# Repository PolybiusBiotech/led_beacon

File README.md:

# 🚨 LED Beacon 🚨

Upgrading cheap LED beacons for professional DMX/Art-Net stage control.

## 🚀 Manufacturing Status
- **Design:** Completed
- **Prototyping:** Completed
- **Production:** Completed

## 📋 Quick Specs
- **Power:** +12V ±30% @ 2A
- **LEDS:** 10x strings of 6 LEDs
- **MCU:** ESP32-C3-WROOM-02
- **Connectivity:** DMX512 via 5 pin XLRs and WiFi

## 📂 Project Structure
- `/hardware`: KiCAD project files (Version 9.0.7).
- `/firmware`: PlatformIO project (Arduino/ESP-IDF framework).
- `/mechanical`: 3D-printable housing (.STEP).
- `/docs`: Specification, schematics and design calculations.
<!-- test: for test scripts -->

## 🛠 Setup & Development

### Hardware
- **Library Dependencies:** All footprints/symbols are [local to the repo / use standard KiCAD libs].
- **CI/CD:** Schematics are automatically exported to `/docs` on every push.

### Firmware
1. Open the `/firmware` folder in **VS Code**.
2. Ensure the **PlatformIO** extension is installed.
3. Connect your hardware via USB C port and click **Upload**.

## 📝 User Guide

1. Apply power via DC connector, 12V ±30% from a 3A capable supply.
2. Attach to DMX chain with 2x XLR 5pin cables
   * If at the end of the bus use a terminator plug
3. Select a DMX address with the DIP switch
   * This light consumes 20 slots so avoid address above 492.
   * Ensure that this light is >20 slots away from the next lights.
   * Light checks DIP switch and updated the DMX address every 2.5seconds.
4. Disable the WiFi AP with the DIP switch unless needed for diagnostics
5. Use your DMX controller to send packets on the DMX chain.
   * Slots 1 to 10 control the brightness per channel
     * `0x00` is off
     * `0xFF` is full brightness
   * Slots 11 to 20 control the strobe effect per channel
     * `0x00` is fully on
     * `0x01` strobes at 0.2Hz
     * `0xFF` strobes at 20Hz
6. Enjoy!

---
*Commissioned for Null Sector for EMF Camp 2026.*

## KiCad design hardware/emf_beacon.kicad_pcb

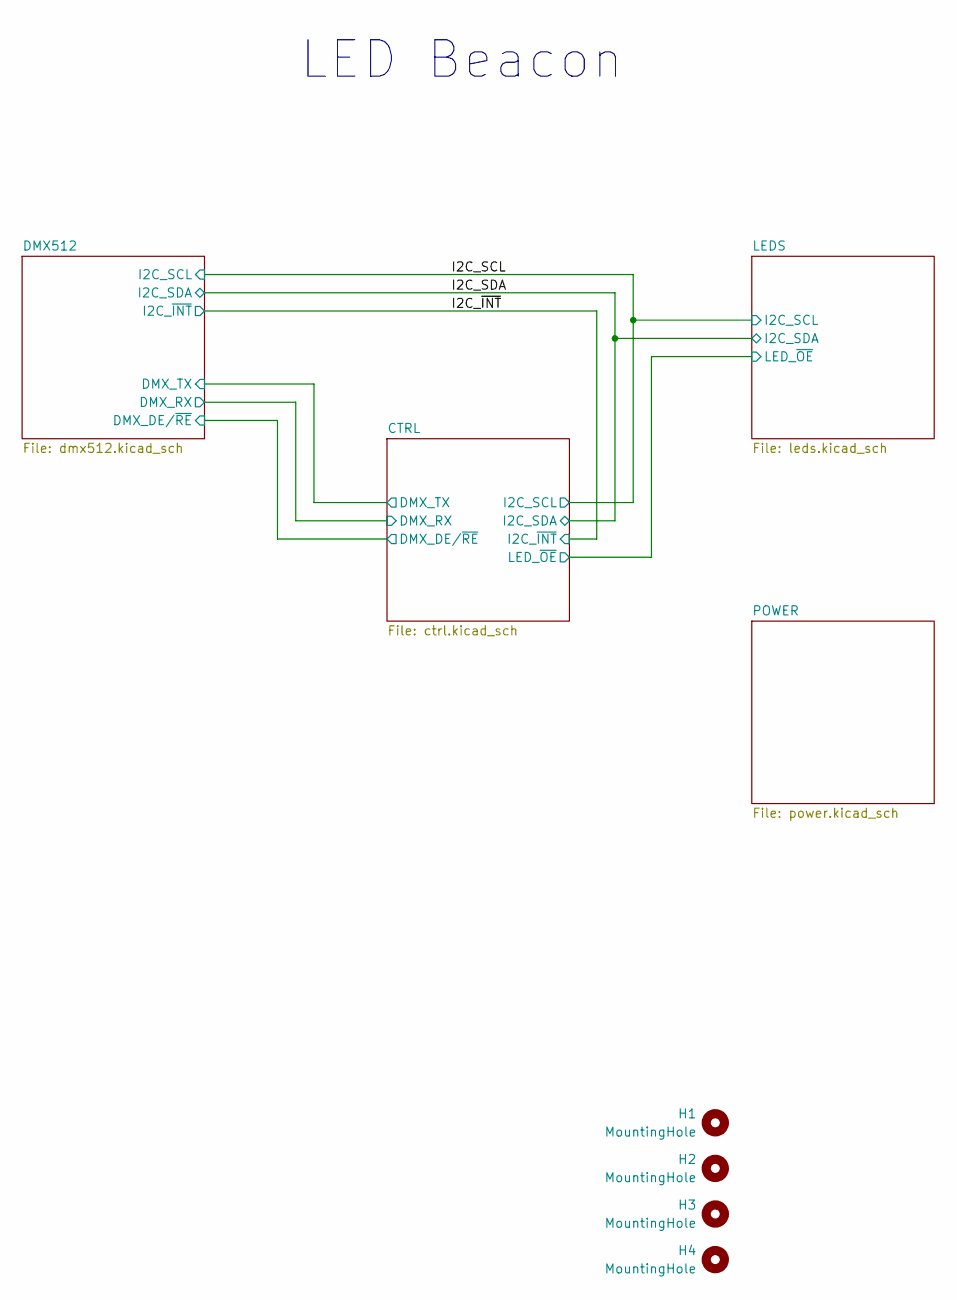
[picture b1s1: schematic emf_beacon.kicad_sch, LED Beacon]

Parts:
H1, H2, H3, H4: MountingHole; MountingHole_4.3mm_M4

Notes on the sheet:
LED Beacon

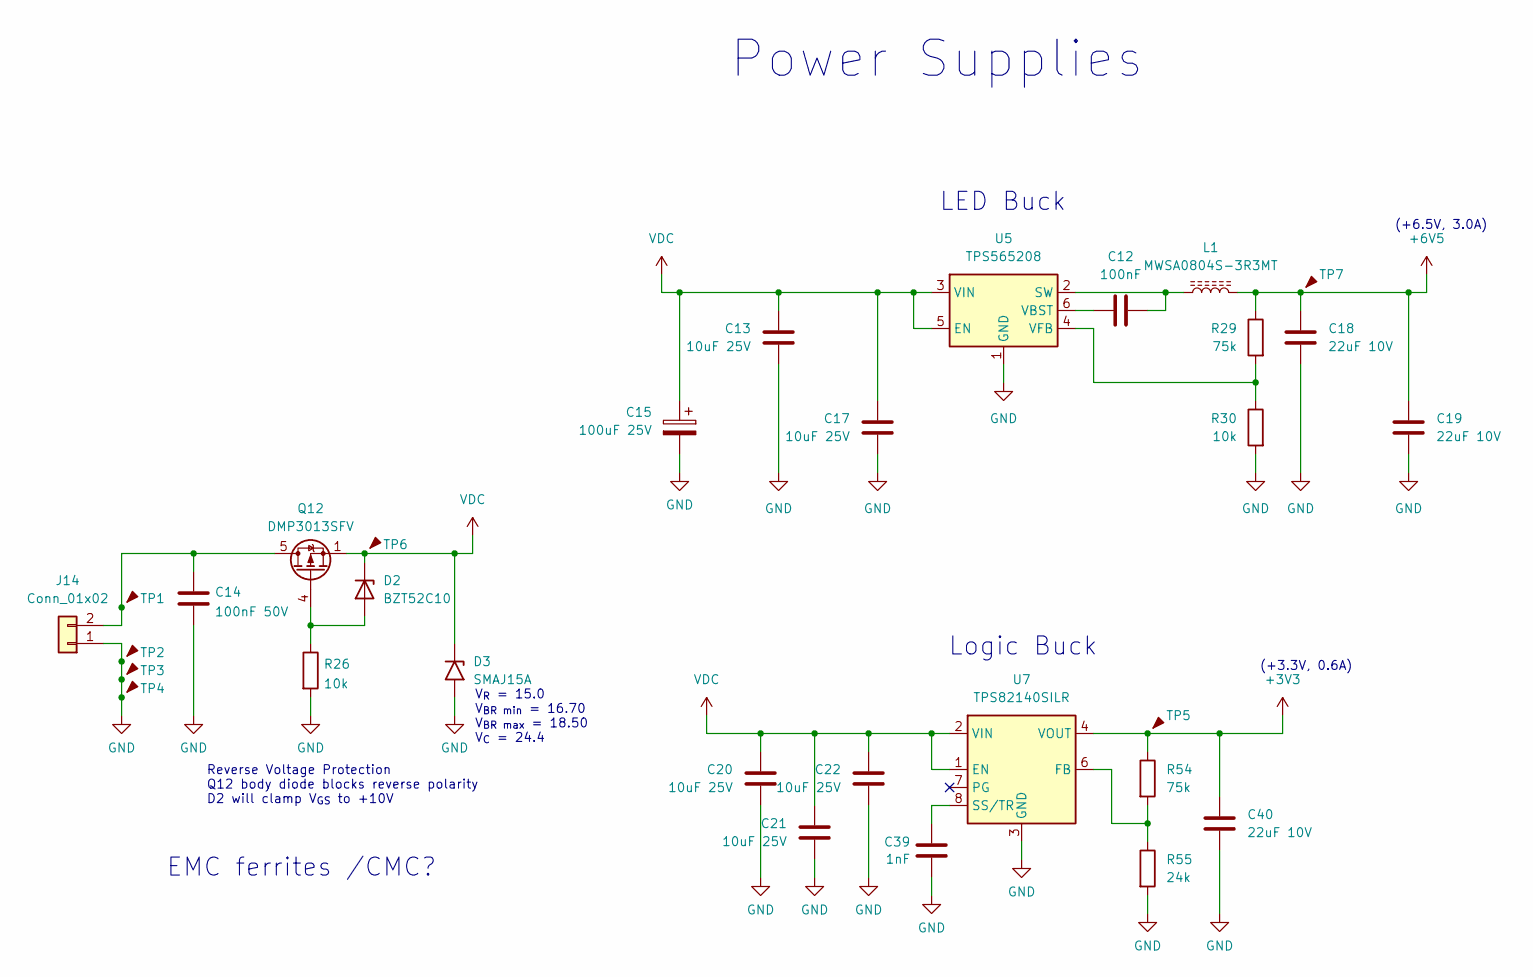
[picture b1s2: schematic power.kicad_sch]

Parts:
C12: 100nF; C_0603_1608Metric; LCSC C14663
C13, C17, C20, C21, C22: 10uF 25V; C_0805_2012Metric; LCSC C15850
C14: 100nF 50V; C_0603_1608Metric; LCSC C14663
C15: 100uF 25V; CP_Elec_6.3x7.7; LCSC C267469
C18, C19: 22uF 10V; C_0805_2012Metric; LCSC C45783
C39: 1nF; C_0603_1608Metric; Voltage 50V; LCSC C1588
C40: 22uF 10V; C_0805_2012Metric; Voltage 10V; LCSC C45783
D2: BZT52C10; D_SOD-123; LCSC C19077408
D3: SMAJ15A; D_SMA; LCSC C19077535
J14: Conn_01x02; MX250-3.5-02P-A-GY01-Cu-A; LCSC C7467028
L1: MWSA0804S-3R3MT; L_Vishay_IHLP-3232; LCSC C17700166
Q12: DMP3013SFV; Diodes_PowerDI3333-8; LCSC C49452326
R26, R30: 10k; R_0603_1608Metric; LCSC C25804
R29, R54: 75k; R_0603_1608Metric; LCSC C23242
R55: 24k; R_0603_1608Metric; LCSC C23352
TP1, TP2, TP3, TP4, TP5, TP6, TP7: TestPoint; TestPoint_Pad_D1.5mm
U5: TPS565208; SOT-23-6; LCSC C2650336
U7: TPS82140SILR; Texas_SIL0008D_MicroSiP-8-1EP_2.8x3mm_P0.65mm_EP1.1x1.9mm; LCSC C544385

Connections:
+3V3: C40.1, R54.1, TP5.1, U7.4 (VOUT), U7.5 (VOUT); also elsewhere on the board
+6V5: C18.1, C19.1, L1.2, R29.1, TP7.1; also elsewhere on the board
GND: C13.2, C14.2, C15.2, C17.2, C18.2, C19.2, C20.2, C21.2, C22.2, C39.2, C40.2, D3.2 (A2), J14.1, R26.2, R30.2, R55.2, TP2.1, TP3.1, TP4.1, U5.1 (GND), U7.3 (GND), U7.9 (GND); also elsewhere on the board
unnamed: D2.2 (A), Q12.4 (G), R26.1
unnamed: C14.1, J14.2, Q12.5 (D), TP1.1
unnamed: C12.2, L1.1, U5.2 (SW)
unnamed: C12.1, U5.6 (VBST)
unnamed: R29.2, R30.1, U5.4 (VFB)
unnamed: R54.2, R55.1, U7.6 (FB)
unnamed: C39.1, U7.8 (SS/TR)
VDC: C13.1, C15.1, C17.1, C20.1, C21.1, C22.1, D2.1 (K), D3.1 (A1), Q12.1 (S), Q12.2 (S), Q12.3 (S), TP6.1, U5.3 (VIN), U5.5 (EN), U7.1 (EN), U7.2 (VIN); also elsewhere on the board

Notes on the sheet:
LED Buck
Power Supplies
V_{R} = 15.0 V_{BR min} = 16.70 V_{BR max} = 18.50 V_{C} = 24.4
Logic Buck
(+6.5V, 3.0A)
EMC ferrites /CMC?
Reverse Voltage Protection Q12 body diode blocks reverse polarity D2 will clamp V_{GS} to +10V
(+3.3V, 0.6A)

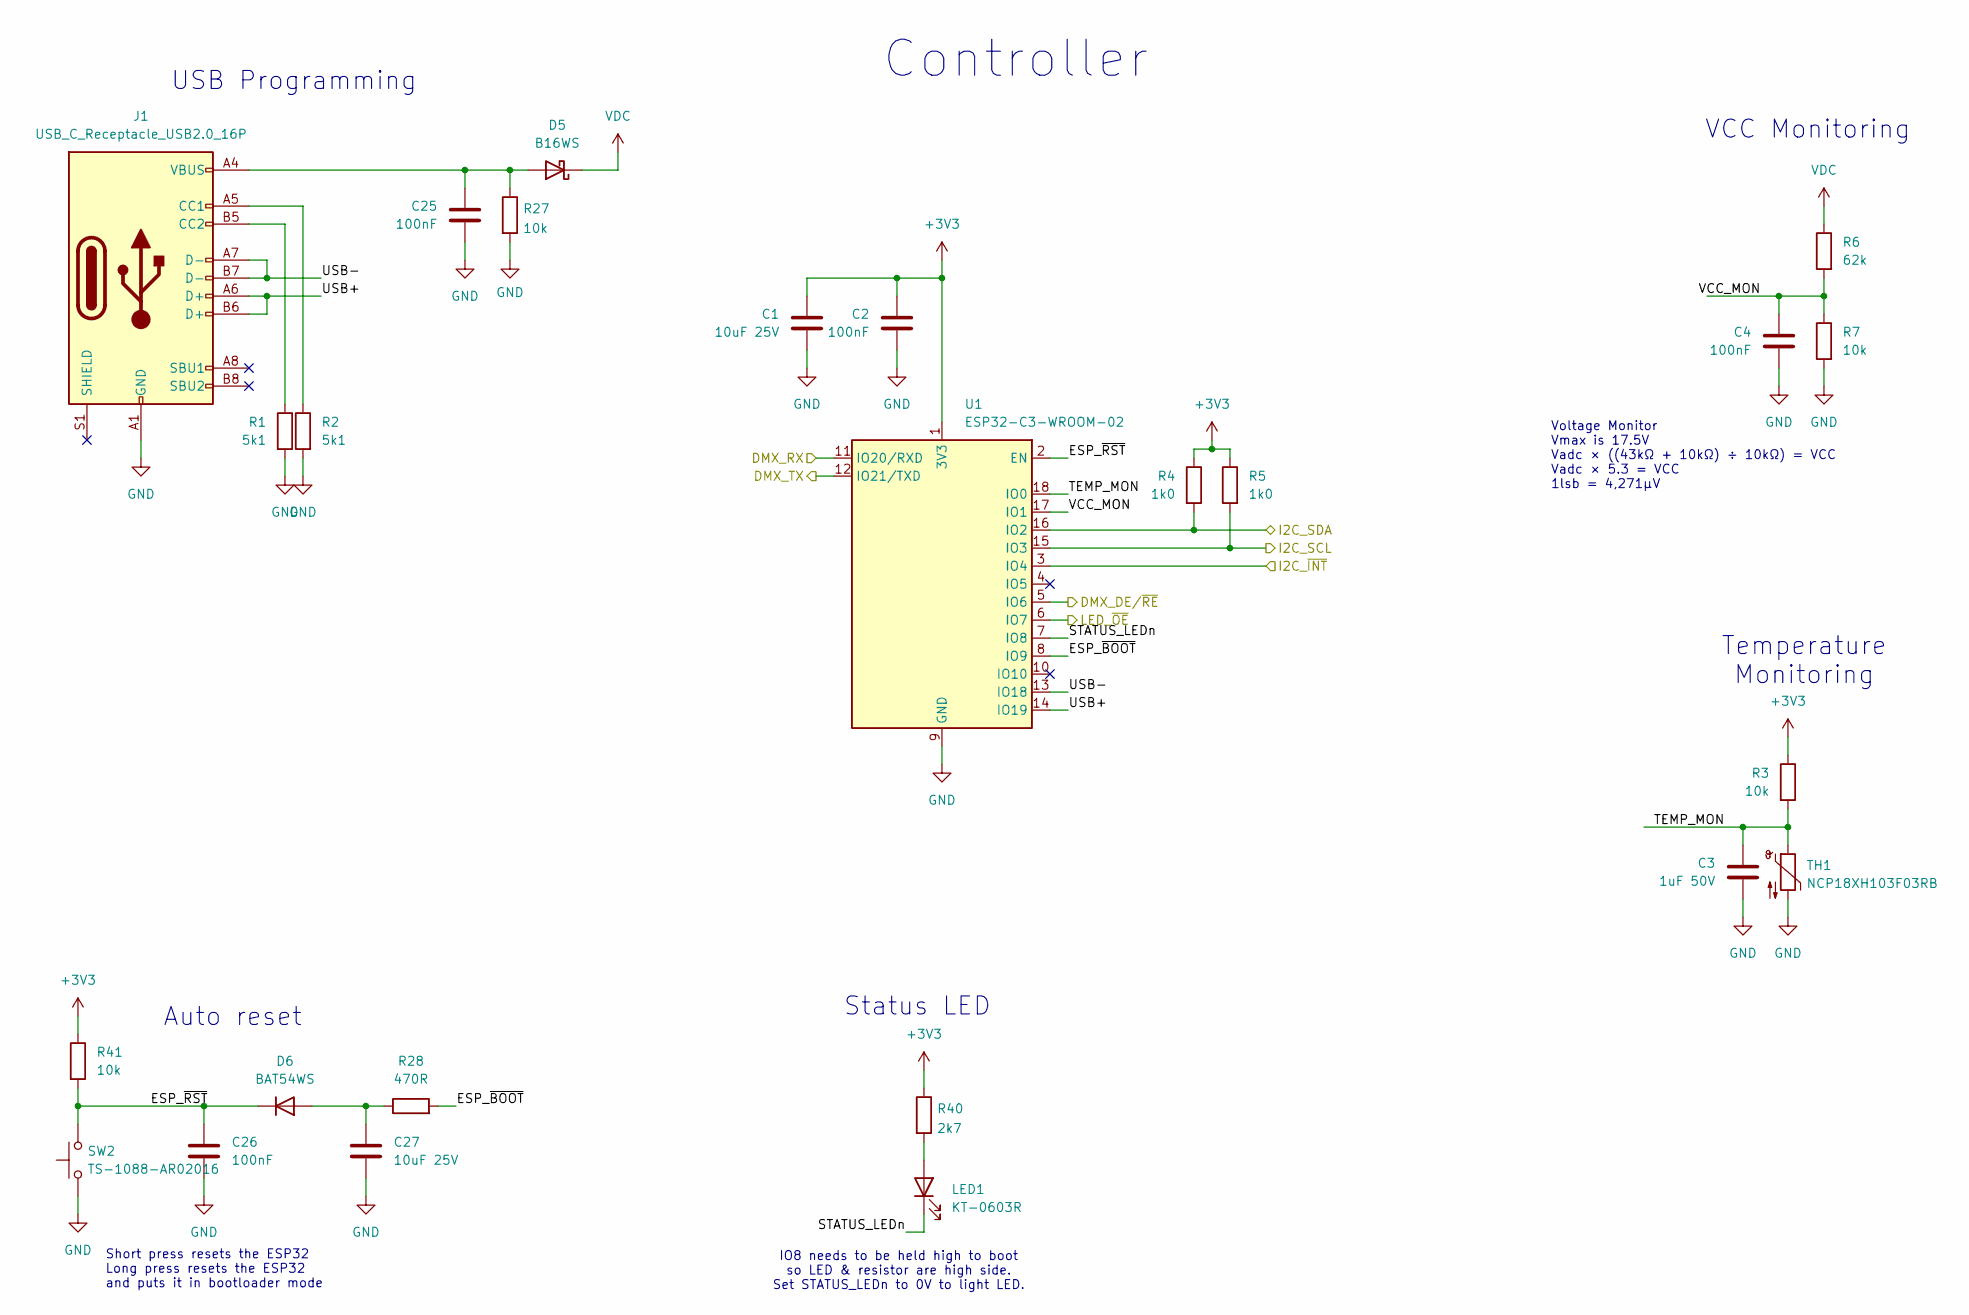
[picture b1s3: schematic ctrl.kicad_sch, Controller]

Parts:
C1, C27: 10uF 25V; C_0805_2012Metric; LCSC C15850
C2, C4, C25, C26: 100nF; C_0603_1608Metric; LCSC C14663
C3: 1uF 50V; C_0603_1608Metric; LCSC C15849
D5: B16WS; D_SOD-323; LCSC C7420327
D6: BAT54WS; D_SOD-323; LCSC C7502694
J1: USB_C_Receptacle_USB2.0_16P; USB_C_Receptacle_HCTL_HC-TYPE-C-16P-01A; LCSC C393939
LED1: KT-0603R; LED_0603_1608Metric; LCSC C2286
R1, R2: 5k1; R_0603_1608Metric; LCSC C23186
R3, R7, R27, R41: 10k; R_0603_1608Metric; LCSC C25804
R4, R5: 1k0; R_0603_1608Metric; LCSC C21190
R6: 62k; R_0603_1608Metric; LCSC C23221
R28: 470R; R_0603_1608Metric; LCSC C23179
R40: 2k7; R_0603_1608Metric; LCSC C13167
SW2: TS-1088-AR02016; SW_Push_SPST_NO_Alps_SKRK; LCSC C720477
TH1: NCP18XH103F03RB; R_0603_1608Metric; MPN NCP18XH103F03RB; LCSC C13564
U1: ESP32-C3-WROOM-02; LCSC C2934560

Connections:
+3V3: C1.1, C2.1, R3.1, R4.1, R5.1, R40.1, R41.1, U1.1 (3V3); also elsewhere on the board
/CTRL/DMX_DE/~RE: U1.5 (IO6); also elsewhere on the board
/CTRL/DMX_RX: U1.11 (IO20/RXD); also elsewhere on the board
/CTRL/DMX_TX: U1.12 (IO21/TXD); also elsewhere on the board
/CTRL/ESP_~BOOT: R28.2, U1.8 (IO9)
/CTRL/ESP_~RST: C26.1, D6.1 (K), R41.2, SW2.2, U1.2 (EN)
/CTRL/LED_~OE: U1.6 (IO7); also elsewhere on the board
/CTRL/STATUS_LEDn: LED1.1 (K), U1.7 (IO8)
/CTRL/TEMP_MON: C3.1, R3.2, TH1.1, U1.18 (IO0)
/CTRL/USB+: J1.A6 (D+), J1.B6 (D+), U1.14 (IO19)
/CTRL/USB-: J1.A7 (D-), J1.B7 (D-), U1.13 (IO18)
/CTRL/VCC_MON: C4.1, R6.2, R7.1, U1.17 (IO1)
/I2C_SCL: R5.2, U1.15 (IO3); also elsewhere on the board
/I2C_SDA: R4.2, U1.16 (IO2); also elsewhere on the board
/I2C_~INT: U1.3 (IO4); also elsewhere on the board
GND: C1.2, C2.2, C3.2, C4.2, C25.2, C26.2, C27.2, J1.A1 (GND), J1.A12 (GND), J1.B1 (GND), J1.B12 (GND), R1.2, R2.2, R7.2, R27.2, SW2.1, TH1.2, U1.9 (GND), U1.19 (GND); also elsewhere on the board
unnamed: C25.1, D5.2 (A), J1.A4 (VBUS), J1.A9 (VBUS), J1.B4 (VBUS), J1.B9 (VBUS), R27.1
unnamed: C27.1, D6.2 (A), R28.1
unnamed: J1.A5 (CC1), R2.1
unnamed: J1.B5 (CC2), R1.1
unnamed: LED1.2 (A), R40.2
VDC: D5.1 (K), R6.1; also elsewhere on the board

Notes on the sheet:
Auto reset
VCC Monitoring
Status LED
Short press resets the ESP32 Long press resets the ESP32 and puts it in bootloader mode
Temperature Monitoring
USB Programming
Controller
IO8 needs to be held high to boot so LED & resistor are high side. Set STATUS_LEDn to 0V to light LED.
Voltage Monitor Vmax is 17.5V Vadc × ((43kΩ + 10kΩ) ÷ 10kΩ) = VCC Vadc × 5.3 = VCC 1lsb = 4,271μV

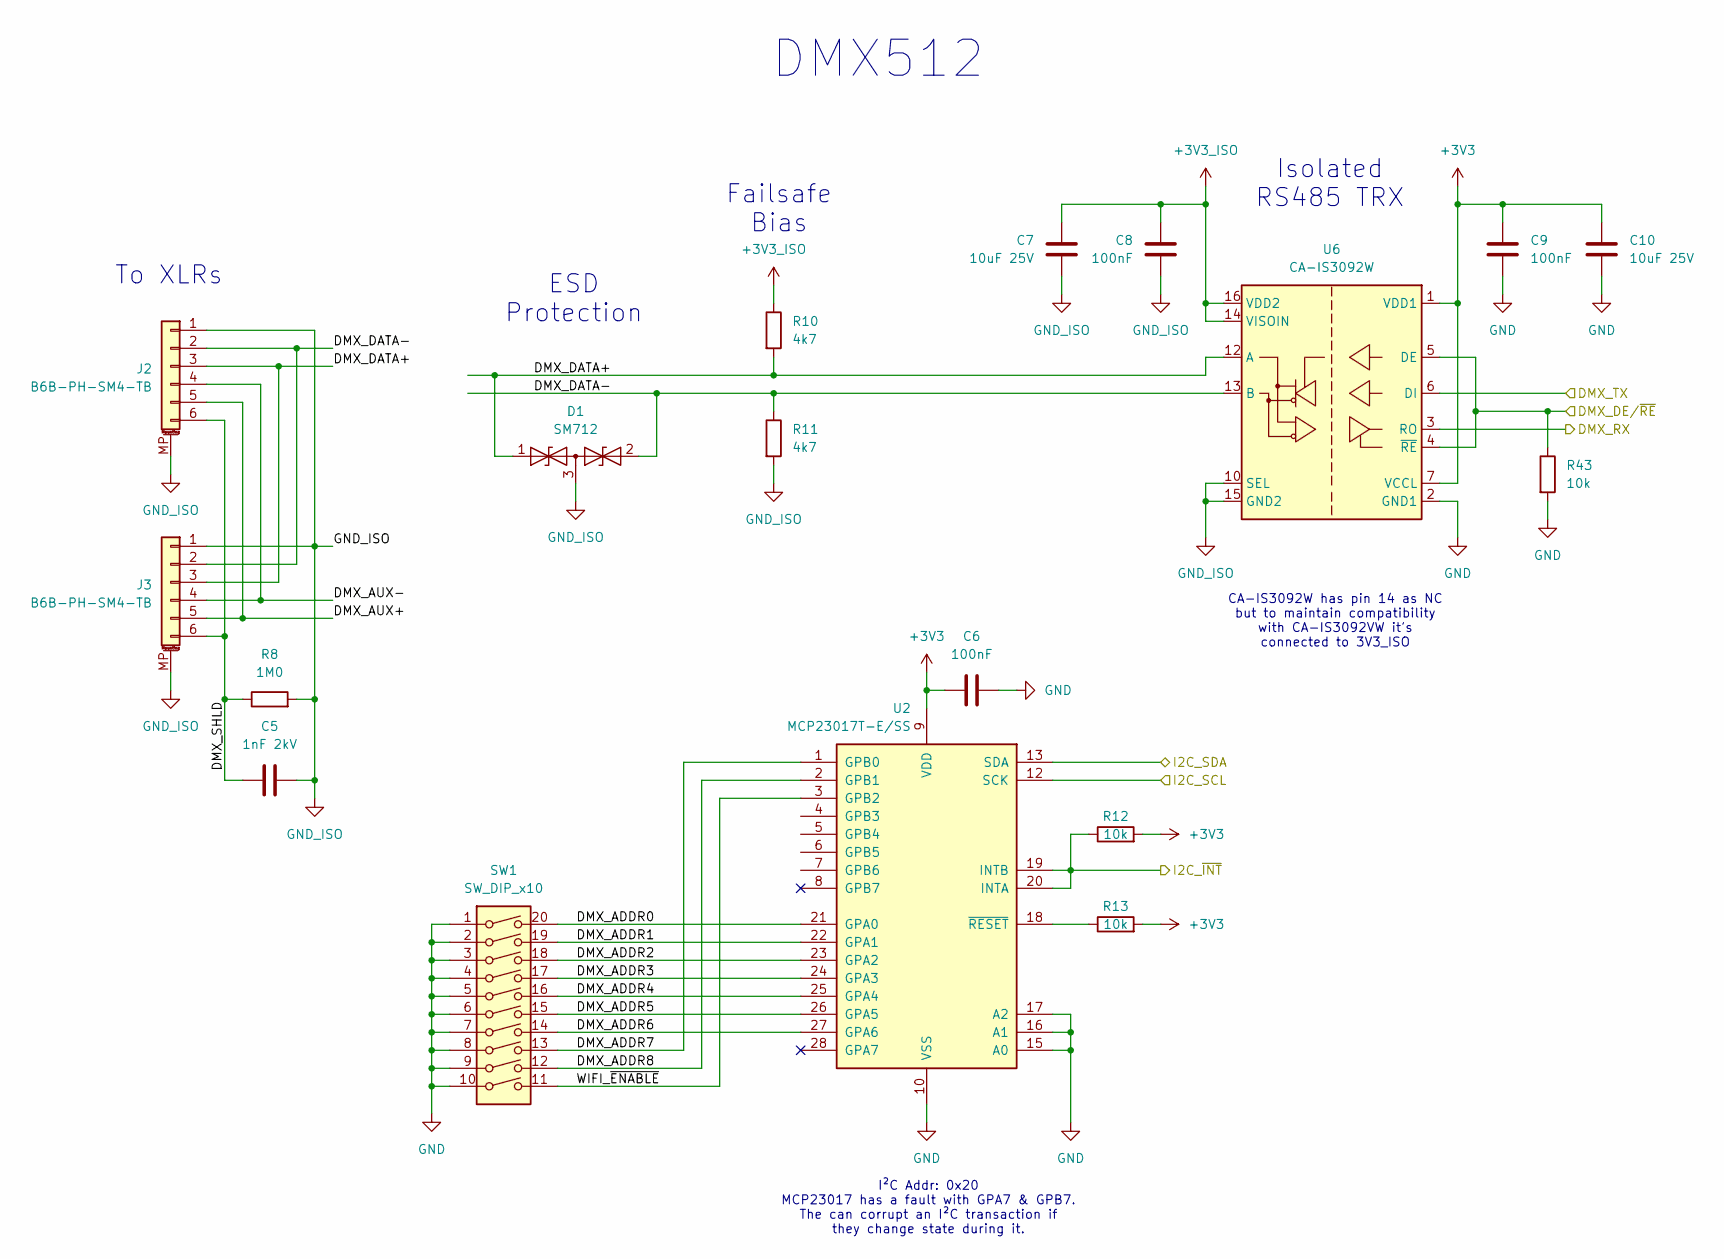
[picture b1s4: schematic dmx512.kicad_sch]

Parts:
C5: 1nF 2kV; C_1206_3216Metric; LCSC C9196
C6, C8, C9: 100nF; C_0603_1608Metric; LCSC C14663
C7, C10: 10uF 25V; C_0805_2012Metric; LCSC C15850
D1: SM712; SOT-23; LCSC C7420375
J2, J3: B6B-PH-SM4-TB; JST_PH_B6B-PH-SM4-TB_1x06-1MP_P2.00mm_Vertical; LCSC C471518
R8: 1M0; R_1206_3216Metric; LCSC C17927
R10, R11: 4k7; R_0603_1608Metric; LCSC C23162
R12, R13, R43: 10k; R_0603_1608Metric; LCSC C25804
SW1: SW_DIP_x10; SW_DIP_SPSTx10_Slide_9.78x27.58mm_W7.62mm_P2.54mm; LCSC C509577
U2: MCP23017T-E/SS; SSOP-28_5.3x10.2mm_P0.65mm; LCSC C558584
U6: CA-IS3092W; SOIC-16W_7.5x10.3mm_P1.27mm; LCSC C2890051

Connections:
+3V3: C6.2, C9.1, C10.1, R12.2, R13.2, U2.9 (VDD), U6.1 (VDD1), U6.7 (VCCL); also elsewhere on the board
+3V3_ISO: C7.1, C8.1, R10.1, U6.14 (VISOIN), U6.16 (VDD2)
/CTRL/DMX_DE/~RE: R43.1, U6.4 (~RE), U6.5 (DE); also elsewhere on the board
/CTRL/DMX_RX: U6.3 (RO); also elsewhere on the board
/CTRL/DMX_TX: U6.6 (DI); also elsewhere on the board
/DMX512/DMX_ADDR0: SW1.20, U2.21 (GPA0)
/DMX512/DMX_ADDR1: SW1.19, U2.22 (GPA1)
/DMX512/DMX_ADDR2: SW1.18, U2.23 (GPA2)
/DMX512/DMX_ADDR3: SW1.17, U2.24 (GPA3)
/DMX512/DMX_ADDR4: SW1.16, U2.25 (GPA4)
/DMX512/DMX_ADDR5: SW1.15, U2.26 (GPA5)
/DMX512/DMX_ADDR6: SW1.14, U2.27 (GPA6)
/DMX512/DMX_ADDR7: SW1.13, U2.1 (GPB0)
/DMX512/DMX_ADDR8: SW1.12, U2.2 (GPB1)
/DMX512/DMX_AUX+: J2.5, J3.5
/DMX512/DMX_AUX-: J2.4, J3.4
/DMX512/DMX_DATA+: D1.1 (A1), J2.3, J3.3, R10.2, U6.12 (A)
/DMX512/DMX_DATA-: D1.2 (A2), J2.2, J3.2, R11.1, U6.13 (B)
/DMX512/DMX_SHLD: C5.1, J2.6, J3.6, R8.1
/DMX512/WIFI_~ENABLE: SW1.11, U2.3 (GPB2)
/I2C_SCL: U2.12 (SCK); also elsewhere on the board
/I2C_SDA: U2.13 (SDA); also elsewhere on the board
/I2C_~INT: R12.1, U2.19 (INTB), U2.20 (INTA); also elsewhere on the board
GND: C6.1, C9.2, C10.2, R43.2, SW1.1, SW1.2, SW1.3, SW1.4, SW1.5, SW1.6, SW1.7, SW1.8, SW1.9, SW1.10, U2.10 (VSS), U2.15 (A0), U2.16 (A1), U2.17 (A2), U6.2 (GND1), U6.8 (GND1); also elsewhere on the board
GND_ISO: C5.2, C7.2, C8.2, D1.3 (common), J2.1, J2.MP (MountPin), J3.1, J3.MP (MountPin), R8.2, R11.2, U6.9 (GND2), U6.10 (SEL), U6.15 (GND2)
unnamed: R13.1, U2.18 (~RESET)

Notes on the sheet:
I²C Addr: 0x20 MCP23017 has a fault with GPA7 & GPB7. The can corrupt an I²C transaction if they change state during it.
Failsafe Bias
DMX512
CA-IS3092W has pin 14 as NC but to maintain compatibility with CA-IS3092VW it's connected to 3V3_ISO
To XLRs
ESD Protection
Isolated RS485 TRX

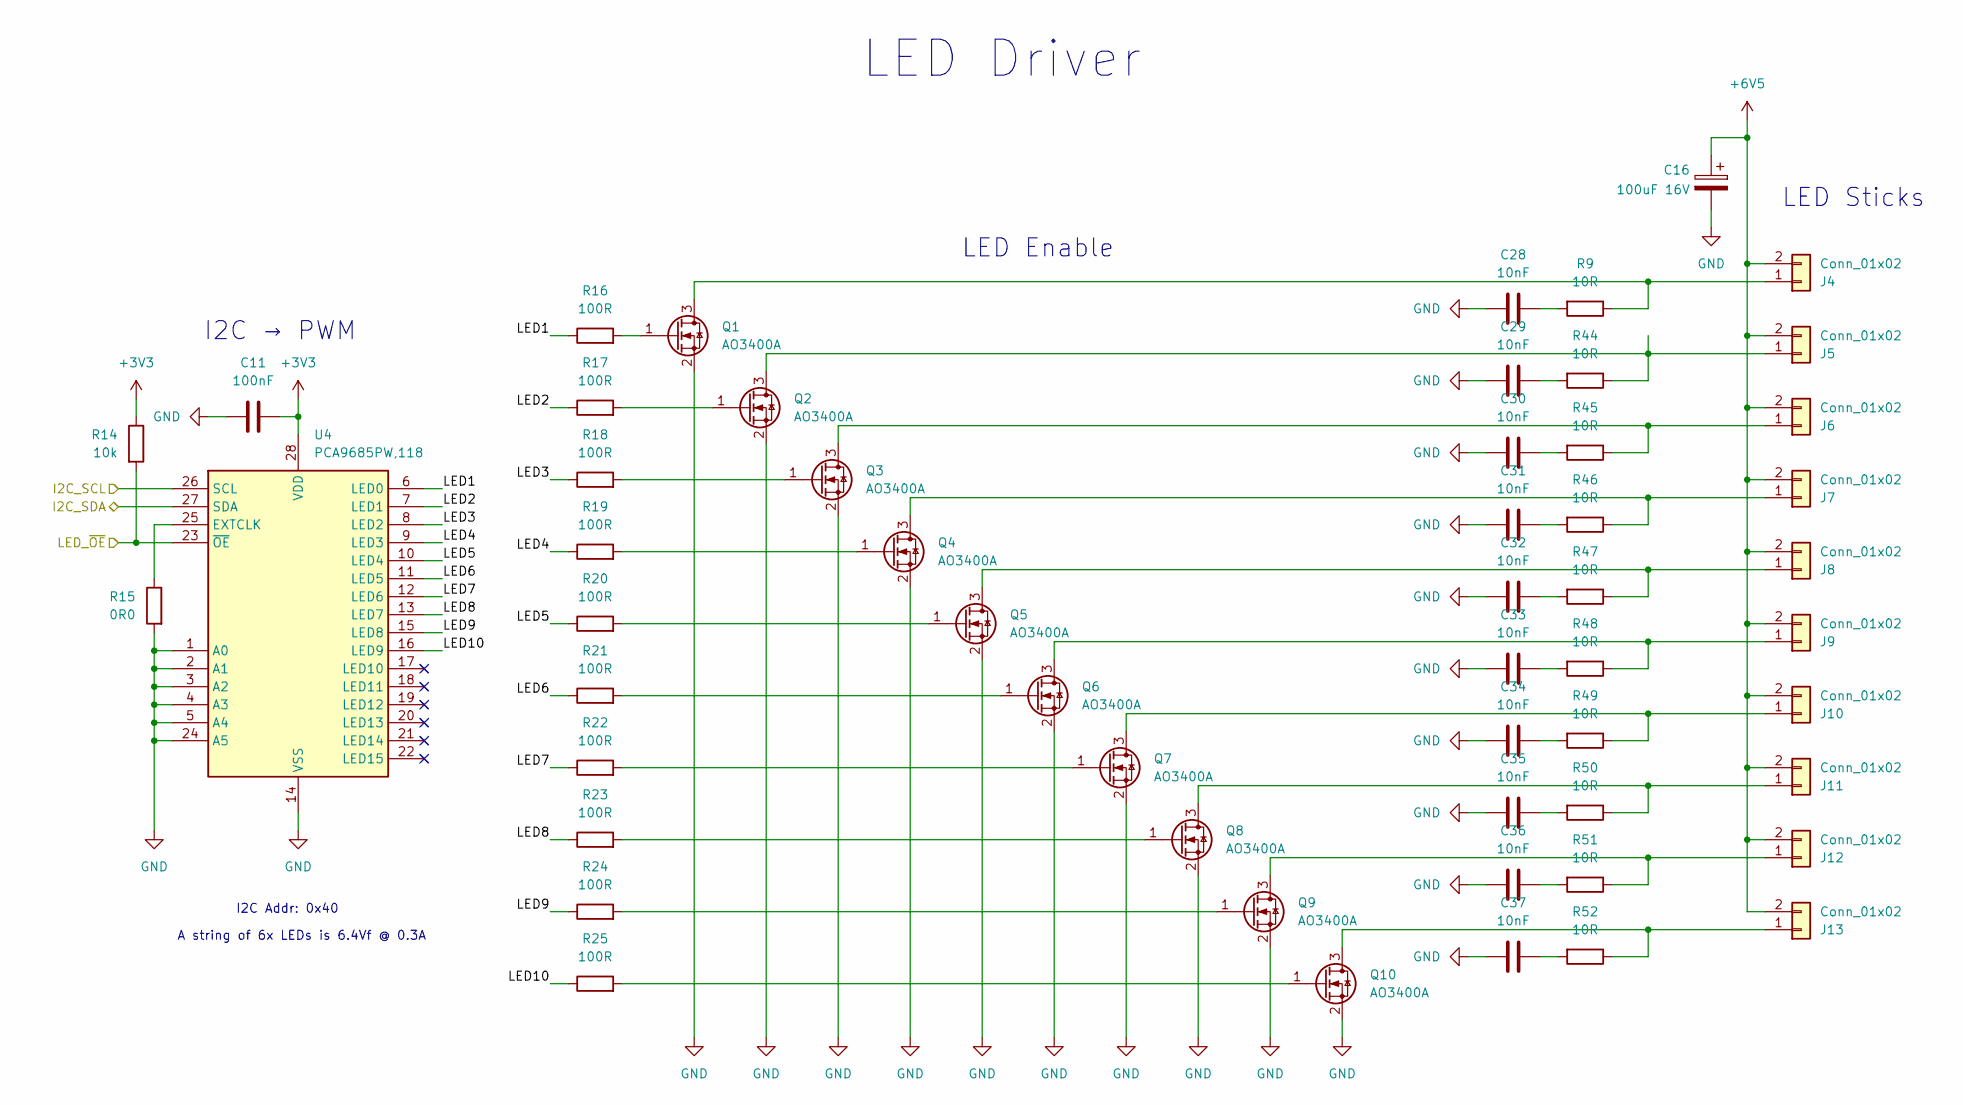
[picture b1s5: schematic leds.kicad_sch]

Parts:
C11: 100nF; C_0603_1608Metric; LCSC C14663
C16: 100uF 16V; CP_Elec_6.3x5.7; LCSC C3646798
C28, C29, C30, C31, C32, C33, C34, C35, C36, C37: 10nF; C_0603_1608Metric; LCSC C57112
J4, J5, J6, J7, J8, J9, J10, J11, J12, J13: Conn_01x02; LED_Stick
Q1, Q2, Q3, Q4, Q5, Q6, Q7, Q8, Q9, Q10: AO3400A; SOT-23; LCSC C20917
R9, R44, R45, R46, R47, R48, R49, R50, R51, R52: 10R; R_0603_1608Metric; LCSC C22859
R14: 10k; R_0603_1608Metric; LCSC C25804
R15: 0R0; R_0603_1608Metric; LCSC C21189
R16, R17, R18, R19, R20, R21, R22, R23, R24, R25: 100R; R_0603_1608Metric; LCSC C22775
U4: PCA9685PW,118; TSSOP-28_4.4x9.7mm_P0.65mm; LCSC C2678753

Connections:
+3V3: C11.2, R14.1, U4.28 (VDD); also elsewhere on the board
+6V5: C16.1, J4.2, J5.2, J6.2, J7.2, J8.2, J9.2, J10.2, J11.2, J12.2, J13.2; also elsewhere on the board
/CTRL/LED_~OE: R14.2, U4.23 (~OE); also elsewhere on the board
/I2C_SCL: U4.26 (SCL); also elsewhere on the board
/I2C_SDA: U4.27 (SDA); also elsewhere on the board
/LEDS/LED1: R16.1, U4.6 (LED0)
/LEDS/LED2: R17.1, U4.7 (LED1)
/LEDS/LED3: R18.1, U4.8 (LED2)
/LEDS/LED4: R19.1, U4.9 (LED3)
/LEDS/LED5: R20.1, U4.10 (LED4)
/LEDS/LED6: R21.1, U4.11 (LED5)
/LEDS/LED7: R22.1, U4.12 (LED6)
/LEDS/LED8: R23.1, U4.13 (LED7)
/LEDS/LED9: R24.1, U4.15 (LED8)
/LEDS/LED10: R25.1, U4.16 (LED9)
GND: C11.1, C16.2, C28.1, C29.1, C30.1, C31.1, C32.1, C33.1, C34.1, C35.1, C36.1, C37.1, Q1.2 (S), Q2.2 (S), Q3.2 (S), Q4.2 (S), Q5.2 (S), Q6.2 (S), Q7.2 (S), Q8.2 (S), Q9.2 (S), Q10.2 (S), R15.2, U4.1 (A0), U4.2 (A1), U4.3 (A2), U4.4 (A3), U4.5 (A4), U4.14 (VSS), U4.24 (A5); also elsewhere on the board
unnamed: C28.2, R9.2
unnamed: C29.2, R44.2
unnamed: C30.2, R45.2
unnamed: C31.2, R46.2
unnamed: C32.2, R47.2
unnamed: C33.2, R48.2
unnamed: C34.2, R49.2
unnamed: C35.2, R50.2
unnamed: C36.2, R51.2
unnamed: C37.2, R52.2
unnamed: J4.1, Q1.3 (D), R9.1
unnamed: J5.1, Q2.3 (D), R44.1
unnamed: J6.1, Q3.3 (D), R45.1
unnamed: J7.1, Q4.3 (D), R46.1
unnamed: J8.1, Q5.3 (D), R47.1
unnamed: J9.1, Q6.3 (D), R48.1
unnamed: J10.1, Q7.3 (D), R49.1
unnamed: J11.1, Q8.3 (D), R50.1
unnamed: J12.1, Q9.3 (D), R51.1
unnamed: J13.1, Q10.3 (D), R52.1
unnamed: Q1.1 (G), R16.2
unnamed: Q2.1 (G), R17.2
unnamed: Q3.1 (G), R18.2
unnamed: Q4.1 (G), R19.2
unnamed: Q5.1 (G), R20.2
unnamed: Q6.1 (G), R21.2
unnamed: Q7.1 (G), R22.2
unnamed: Q8.1 (G), R23.2
unnamed: Q9.1 (G), R24.2
unnamed: Q10.1 (G), R25.2
unnamed: R15.1, U4.25 (EXTCLK)

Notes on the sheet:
I2C → PWM
A string of 6x LEDs is 6.4Vf @ 0.3A
I2C Addr: 0x40
LED Enable
LED Driver
LED Sticks

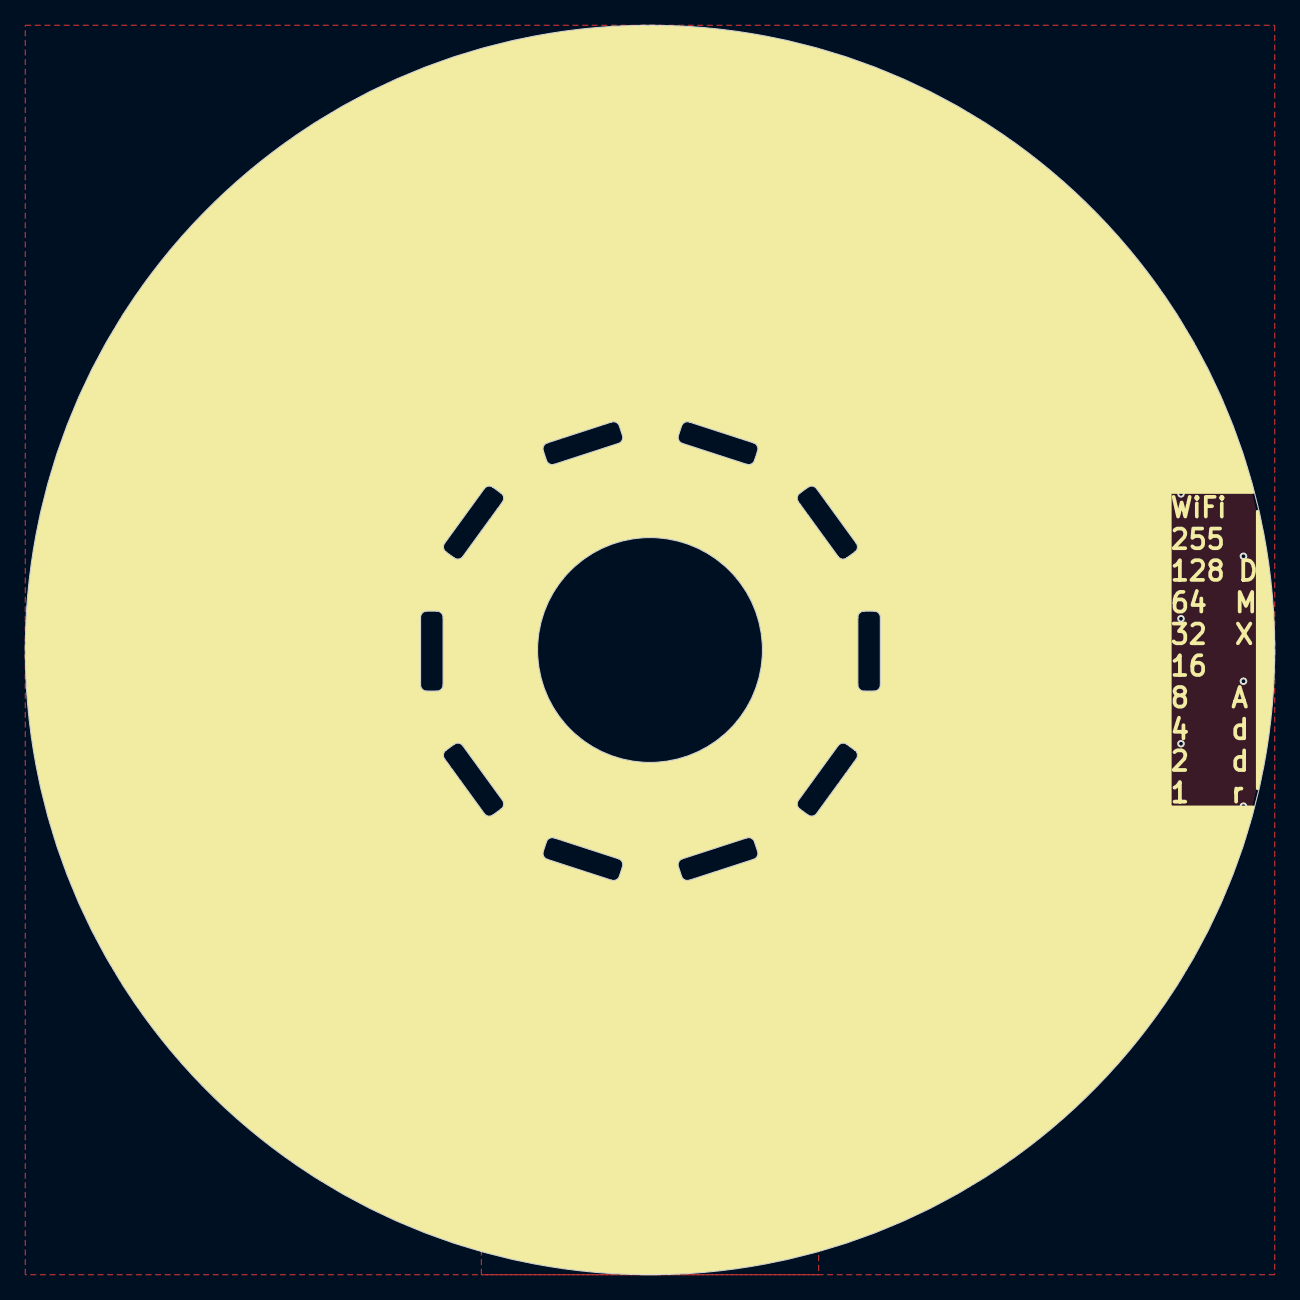
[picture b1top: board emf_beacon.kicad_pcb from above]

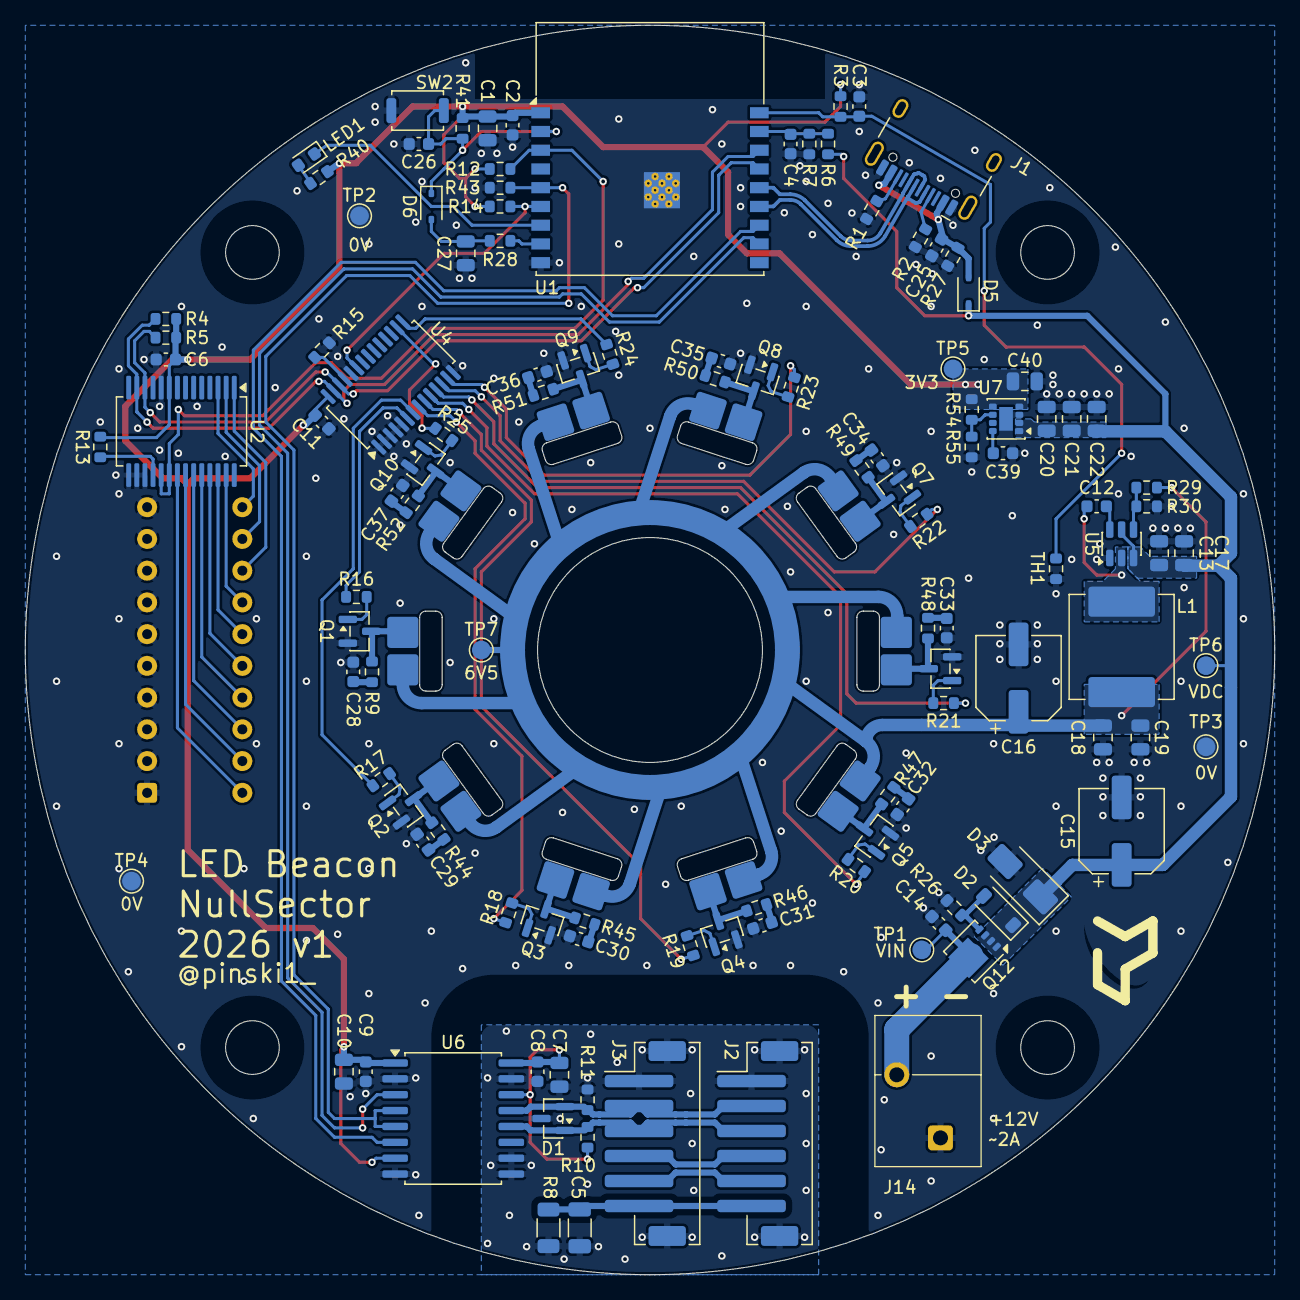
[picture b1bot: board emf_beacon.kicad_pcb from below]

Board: 2 copper layers, 100.0 x 100.0 mm, 133 parts (128 on the bottom side), 89 nets.

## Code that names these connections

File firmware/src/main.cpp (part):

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const char* wifi_pass = "password123";

/** Pin Map **/
#define PIN_TEMP_MON  (0)
#define PIN_VCC_MON   (1)
#define PIN_SDA       (2)
#define PIN_SCL       (3)
#define PIN_I2C_INT   (4)
#define PIN_WIFI_EN   (5)
#define PIN_DMX_EN    (6)
#define PIN_LED_OE    (7)
#define PIN_STATE_LED (8)
#define PIN_DMX_RX   (20)
#define PIN_DMX_TX   (21)

/** Hardware instantiations  **/
Adafruit_PWMServoDriver leds = Adafruit_PWMServoDriver(0x40);
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  Serial.write(init_string);

  // init GPIO
  pinMode(PIN_I2C_INT, INPUT);
  pinMode(PIN_LED_OE, OUTPUT);
  pinMode(PIN_DMX_EN, OUTPUT);
  pinMode(PIN_WIFI_EN, INPUT_PULLUP);
  pinMode(PIN_STATE_LED, OUTPUT);
  digitalWrite(PIN_LED_OE, HIGH);  // disable LEDs
  digitalWrite(PIN_DMX_EN, LOW);
  digitalWrite(PIN_STATE_LED, LOW);
  analogSetAttenuation(ADC_11db);
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  leds.setOutputMode(true);  // LEDs driven by external NMOS
  for (int i = 0; i < led_count; i++) leds.setPWM(i, 0x000, 0x1000);  // sets LED[i]_OFF_H bit
  delay(1);  // takes a PWM cycle to update
  digitalWrite(PIN_LED_OE, LOW);  // enable LEDs!
  Serial.println("PCA9685 initialised...");

  // init DMX
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  };
  int personality_count = 1;
  dmx_driver_install(dmx_num, &config, personalities, personality_count);
  dmx_set_pin(dmx_num, PIN_DMX_TX, PIN_DMX_RX, PIN_DMX_EN);
  Serial.println("DMX initialised...");

  // init Watchdog
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
    // dealing with excessive temp
    if (current_temp >= warning_temp) {
      digitalWrite(PIN_LED_OE, HIGH);  // disable LEDs while too hot!
    } else if (current_temp <= (warning_temp - 5000)) {
      digitalWrite(PIN_LED_OE, LOW);  // enable LEDs now it's cooler
    }

    // not sure what actions to take on over voltage

    // dealing with under voltage
    if (current_volts <= warning_volts) {
      digitalWrite(PIN_LED_OE, HIGH);  // disable LEDs if input voltage is too low!
    } else if (current_volts <= (warning_volts + 3000)) {
      digitalWrite(PIN_LED_OE, LOW);  // enable LEDs now input voltage is higher
    }

    current_uptime = esp_timer_get_time() / 1000000;
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    dmx_adr_switches = (mcp_pin_values & 0x7F) | ((mcp_pin_values & 0x0300) >> 1);
    dmx_address = dmx_adr_switches;  // save DMX address

    wifi_enable = (mcp_pin_values >> 10) & 0x01;

    // enable/disable WiFi AP
    if (wifi_enable && !wifi_ap_active) {
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  int32_t raw_temp = 0x00;

  for (int i = 0; i < 8; i++) {
    raw_temp += analogRead(PIN_TEMP_MON);
    delay(1);
  }
  raw_temp /= 8;
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
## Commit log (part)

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2026-04-20 Adding init files
2026-04-20 inital board files
2026-04-21 adding workflow
2026-04-21 removing 'home' from filenames
2026-04-21 adding ESP32 and PSU options
2026-04-21 docs: auto-generate schematic PDF
2026-04-21 removed Art-Net
2026-04-22 clean up
2026-04-22 updating readme
2026-04-23 adding 3D model of 3D printed beacon base
2026-04-23 inital check in of firmware
2026-04-24 testing PCA9685 and MCP23017 work
2026-04-24 removing I2C scanner
2026-04-25 improving voltage and temperature calcs
2026-04-26 updating thermistor and GPIO expander
2026-04-27 adding LED bightness functionality
2026-04-27 Update main.cpp
    Adding last DMX time to status page
2026-04-27 Update main.cpp
    Told the the server to use the pretty status page.
2026-04-27 adding memory to status page
2026-04-27 adding snubbers, starting placement
2026-04-30 updating PSUs
2026-04-30 adding testing features
2026-04-30 removing art-net.kicad_sch
2026-04-30 some jlc cleanup
2026-04-30 updating documents
2026-05-07 tweaking lcsc part numbers
2026-05-12 Update export_artifacts.yml
    Fixing step export
2026-05-12 docs: auto-generate schematic PDF, 3D model, and rear render
2026-05-12 Adding wiring drawings for XLR pigtails
2026-05-13 general schematic and PCB clean
2026-05-19 Update main.cpp
    Combining memory & system cards
2026-05-21 sorting button and LED
2026-05-24 starting layout
2026-05-25 adding DRU for DMX isolation
2026-05-25 moving all parts into project libraries
2026-05-25 more layout and fixing OOS items
2026-06-02 LEDs connected
2026-06-03 updating DMX TRX and improving silkscreen
2026-06-03 routing VDC
2026-06-03 fixing terminal block pads
2026-06-04 finished USB routing
2026-06-04 finished NTC routing
2026-06-04 ran DRC & DFM checks, looks good
2026-06-05 adding stitching vias
2026-06-05 reviewed LED connections and found a fault
2026-06-05 unswapped LEDs
2026-06-05 preparing for release
2026-06-09 tweaking wiring drawings
2026-06-09 removing old base files
2026-06-09 adding wiring diagram generator
2026-06-09 chore: auto-generate WireViz PDFs from mechanical/ [skip ci]
2026-06-10 adding svg to pdf for wireviz
2026-06-22 support for high DMX Addresses and LED test pattern
2026-06-27 added WiFi AP enable/disable
2026-06-28 fixed WiFi AP enable/disable
2026-06-28 LEDs don't flash on boot
